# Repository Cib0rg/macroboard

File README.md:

# ESP32-S3 Macro Keyboard

Программируемая макроклавиатура с открытым исходным кодом на базе ESP32-S3 — 10 кнопок с индивидуальными круглыми дисплеями, RGB подсветкой и настраиваемыми действиями.

## Обзор

Устройство аналогично Elgato Stream Deck, но с открытым исходным кодом. Каждая кнопка имеет собственный круглый дисплей 160×160 для отображения иконок, RGB LED подсветку и программируемое действие.
Отсутствует ограничение по входному напряжению, подключение зарядок с QC скорее всего сожжёт часть платы!
Включать сначала питание от 2А блока (нижний разъём), потом уже подключать ESP через встроенные. Иначе есть небольшой шанс выхода из строя DC-DC преобразователя на плате ESP.

## Реализованные возможности

### Прошивка (Firmware)

- ✅ **Драйвер дисплеев GC9A01** — 10 круглых дисплеев 160×160 через SPI с мультиплексором 2× 74HC138
- ✅ **PWM подсветка дисплеев** — регулировка яркости 0-255 через LEDC
- ✅ **WS2812 RGB LED** — индивидуальная подсветка каждой кнопки с настройкой цвета и яркости
- ✅ **USB Composite Device** — HID Keyboard + Consumer Control + Vendor Bulk (TinyUSB)
- ✅ **Протокол обмена** — 64-байтовые пакеты через Vendor Bulk endpoint
- ✅ **Конфигурация** — хранение настроек кнопок и энкодера в LittleFS
- ✅ **Папки** — вложенные папки кнопок (до 8 уровней глубины)
- ✅ **Передача изображений** — JPEG изображения на кнопки с дедупликацией по CRC32
- ✅ **Асинхронная запись LittleFS** — `save_task` на Core 0, очередь 20 слотов; протокол не блокируется на I/O, sync fallback при нехватке слотов; полная синхронизация ~17 изображений: ~11 с вместо ~39 с
- ✅ **LittleFS хранилище текстов** — тексты до 4096 байт в LittleFS по 5-компонентному ключу `(profile/folder/button/action_slot/step_index)`; покрывает: Keyboard > 44 байт, long press Keyboard, каждый шаг Sequence с длинным текстом, Sequence-блоб > 51 байт
- ✅ **Rotary encoder** — настраиваемые действия на CW/CCW/нажатие/долгое нажатие
- ✅ **Долгое нажатие** — отдельное действие и название для каждой кнопки (корневой и в папках)
- ✅ **Debounced кнопки** — обработка нажатий через прерывания с программным debounce
- ✅ **Действия кнопок**: Keyboard, Media (Consumer Control), Shell, Folder, Sequence, CustomHID, LaunchApp, NightMode

### Управляющий софт (Software)

- ✅ **Кроссплатформенный UI** — Avalonia UI (Linux, Windows, macOS)
- ✅ **Backend Service** — фоновый сервис для связи с устройством
- ✅ **IPC** — TCP-based коммуникация между UI и Backend с автоматическим переподключением
- ✅ **Редактор конфигурации** — создание, редактирование, синхронизация конфигураций с устройством (JSON)
- ✅ **Конфигурация кнопок** — inline-редактор с поддержкой всех типов действий
- ✅ **Захват клавиш** — запись комбинаций клавиш в реальном времени
- ✅ **Последовательности действий** — до 16 шагов с задержками
- ✅ **Медиа-клавиши** — Volume Up/Down, Mute, Play/Pause, Next/Prev Track
- ✅ **Превью изображений** — миниатюры в списке кнопок и превью в редакторе
- ✅ **Настройка LED** — выбор цвета через ColorPicker, яркость
- ✅ **Настройка подсветки дисплеев** — слайдер яркости в Dashboard и Settings
- ✅ **Tray icon** — работа в фоне, сворачивание в трей
- ✅ **Dashboard** — статус устройства, лог событий, управление яркостью
- ✅ **Diff-based синхронизация профиля** — при Send пересылаются только изменённые кнопки; fingerprint учитывает image path+mtime, action type+JSON, LED; типовая правка одной кнопки: ~5 с; холодная синхронизация ~17 изображений: ~11 с (async SPIFFS)
- ✅ **Синхронизация с устройством** — отправка/загрузка профилей через USB
- ✅ **Сохранение профиля** — Save пишет в исходный файл (откуда был загружен через Load), а не в AppData
- ✅ **LibUsbDotNet** — кроссплатформенная USB коммуникация (Linux/Windows/macOS)
- ✅ **Плагины (Stream Deck совместимость)** — запуск `.streamDeckPlugin` архивов и исполняемых плагинов, WebSocket API на порту 28196, Property Inspector на порту 8787; плагины хранятся в `plugins/` рядом с бинарником бэкенда
- ✅ **Валидация ввода** — Shell-команда ≤ 49 байт UTF-8, Custom HID ≤ 51 байт (соответствует `ACTION_DATA_MAX_LEN` прошивки); превышение показывает ошибку вместо молчаливой обрезки
- ✅ **Кэш иконок приложений** — иконки извлекаются один раз через P/Invoke и сохраняются в `%APPDATA%\MacroKeyboard\icons\`; повторное открытие диалога не вызывает P/Invoke

## Плагины

MacroKeyboard поддерживает плагины в стиле Elgato Stream Deck. Каждая кнопка может быть привязана к действию стороннего плагина, который получает события нажатий и управляет дисплеем.

Два режима работы:
- **Executable** — отдельный процесс на любом языке (C#, Node.js, Python), общается с бекендом через WebSocket на порту 28196.
- **Managed** — .NET DLL, загружается в процесс бекенда, получает прямой доступ к устройству через `IPlugin` / `IPluginContext`.

Плагины кладутся в папку `plugins/` рядом с бинарником бекенда в виде директории или `.zip`-архива с расширением `.sdPlugin`. Существующие плагины для Stream Deck работают с минимальными изменениями.

Подробное руководство по разработке плагинов: **[PLUGIN_DEVELOPMENT.html](PLUGIN_DEVELOPMENT.html)**

## Структура проекта

```
elgato/
├── firmware/                    # Прошивка ESP32-S3 (ESP-IDF v5.4, C)
│   └── main/
│       ├── hardware/            # Драйверы: дисплеи, LED, кнопки, энкодер
│       ├── profile/             # Менеджер профилей, исполнитель действий
│       ├── protocol/            # Обработчик протокола, передача изображений и текста
│       ├── storage/             # NVS, LittleFS, профили, изображения, длинный текст, async save_task
│       └── usb/                 # USB дескрипторы, HID keyboard, vendor endpoint
│
├── hardware/                    # Аппаратная часть
│   ├── case/                    # 3D-модели корпуса (OpenSCAD + STL для печати)
│   └── pcb/                     # Схемотехника и разводка PCB (KiCad)
│
├── software/                    # Управляющее приложение (.NET 10, C#)
│   └── src/
│       ├── MacroKeyboard.Core/          # Модели, IPC, интерфейсы сервисов
│       ├── MacroKeyboard.Communication/ # USB протокол, команды устройства
│       ├── MacroKeyboard.Infrastructure/# Реализация сервисов, репозитории
│       ├── MacroKeyboard.Backend/       # Фоновый сервис (IPC сервер, роутинг)
│       └── MacroKeyboard.UI/            # Avalonia UI (MVVM, CommunityToolkit)
│
└── plans/                       # Проектная документация
```

## Быстрый старт

### Сборка прошивки

```bash
cd firmware
# Через Docker (рекомендуется):
docker run --rm -v "$(pwd)":/project -w /project espressif/idf:v5.4 idf.py build
# Или локально с установленным ESP-IDF v5.4:
idf.py build
idf.py flash
```

### Сборка софта

```bash
cd software
dotnet build MacroKeyboard.sln
# Запуск Backend:
dotnet run --project src/MacroKeyboard.Backend
# Запуск UI:
dotnet run --project src/MacroKeyboard.UI
```

### Linux: доступ к USB без root

```bash
sudo cp software/scripts/99-macrokeyboard.rules /etc/udev/rules.d/
sudo udevadm control --reload-rules
```

## Технологии

### Прошивка

| Компонент | Технология |
|-----------|-----------|
| Платформа | ESP32-S3 N16R8 (16MB Flash, 8MB PSRAM) |
| Framework | ESP-IDF v5.4 |
| RTOS | FreeRTOS |
| USB | TinyUSB (HID + Vendor composite) |
| Язык | C99 |

### Софт

| Компонент | Технология |
|-----------|-----------|
| Runtime | .NET 10 |
| UI | Avalonia UI 12 |
| Архитектура | MVVM (CommunityToolkit.Mvvm) |
| USB | LibUsbDotNet 3.x |
| Изображения | SixLabors.ImageSharp |
| Сериализация | Newtonsoft.Json |
| Логирование | Serilog |

## Аппаратные компоненты

| Компонент | Модель | Кол-во | Примечания |
|-----------|--------|--------|------------|
| Микроконтроллер | ESP32-S3 N16R8 | 1 | 16MB Flash, 8MB PSRAM |
| Дисплей | GC9A01 160×160 | 10 | Круглые TFT, SPI |
| Кнопки | Тактовые | 10 | GPIO с прерываниями |
| RGB LED | WS2812 | 10 | Адресные, RMT peripheral |
| Энкодер | Rotary encoder | 1 | С кнопкой |
| Мультиплексор | 74HC138 | 2 | Выбор дисплея (5+5) |

Схемотехника и разводка PCB находятся в директории [`hardware/pcb/`](hardware/pcb/) (формат KiCad).
3D-модели корпуса для печати — в [`hardware/case/`](hardware/case/) (OpenSCAD + STL).

## Протокол обмена данными

64-байтовые пакеты через USB Vendor Bulk endpoint:

```
[0]    Magic (0xA5)
[1]    Command ID
[2-3]  Payload Length
[4-5]  Sequence Number
[6-61] Payload (56 bytes)
[62]   Checksum (XOR)
[63]   End Byte (0x5A)
```

### Команды

| ID | Команда | Описание |
|----|---------|----------|
| 0x01 | PING | Проверка связи |
| 0x02 | GET_DEVICE_INFO | Информация об устройстве |
| 0x10 | SET_PROFILE | Активировать профиль |
| 0x11–0x12 | GET_PROFILE_INFO / FOLDER_STATE | Состояние профиля и текущей папки |
| 0x20–0x22 | IMAGE_TRANSFER | Передача изображений (start/chunk/end) |
| 0x30–0x34 | BUTTON_ACTION/NAME | Установка действия и имени кнопки (корневые и папки) |
| 0x35 | SET_ENCODER_ACTION | Настройка действий энкодера |
| 0x36–0x37 | LONG_PRESS_ACTION/NAME | Действие и название долгого нажатия |
| 0x38–0x3A | TEXT_TRANSFER | Передача текста/блоба в SPIFFS (start/chunk/end); Keyboard > 44 байт, long press, Sequence-шаги и блобы > 51 байт |
| 0x40–0x43 | LED/BACKLIGHT | Управление LED и подсветкой дисплеев |
| 0x50–0x53 | PROFILE_SAVE/LOAD/DELETE/REFRESH | Управление профилями и обновление дисплеев |

### Типы действий

| ID | Тип | Описание |
|----|-----|----------|
| 0x01 | Keyboard | Эмуляция клавиатуры; текст ≤ 44 байт — inline, > 44 байт — SPIFFS |
| 0x02 | CustomHID | Произвольный HID report |
| 0x04 | Folder | Открытие папки кнопок |
| 0x06 | Shell | Выполнение shell-команды на PC |
| 0x07 | Sequence | Последовательность до 16 действий |
| 0x08 | LaunchApp | Запуск приложения на PC |
| 0x09 | Media | Медиа-клавиши (Volume, Mute, Play/Pause и др.) |
| 0x0A | NightMode | Переключение ночного режима (снижение яркости) |
| 0x0B | Plugin | Действие стороннего плагина (Stream Deck-совместимого) |

### LittleFS-хранилище текстов

Команды 0x38–0x3A передают текстовые данные, которые не влезают inline. На устройстве файл называется `/storage/txt_{P}_{F}_{B}_{A}_{S}.bin`, где:

| Поле | Смысл |
|------|-------|
| P | profile_id (всегда 0) |
| F | folder_id: 0..15 = папка, 255 = root |
| B | button_id: 0..9; энкодер: 0x40–0x43 |
| A | action slot: 0 = short press, 1 = long press |
| S | step: 0xFF = прямое Keyboard, 0xFE = Sequence-блоб, 0..15 = шаг Sequence |

Что хранится в SPIFFS:
- **Keyboard** текст > 44 байт — `step=0xFF` (short), `step=0xFF, slot=1` (long press)
- **Sequence-шаг Keyboard** > 44 байт — `step=N` (индекс шага)
- **Sequence-блоб** > 51 байт — `step=0xFE`; в `action_data` кнопки записывается маркер `[0x01]`

ПО автоматически выбирает между inline и SPIFFS. Payload CMD_SET_BUTTON_TEXT_START: 9 байт — `[profile_id][folder_id][button_id][action_slot][step_index][data_size(4 LE)]`.

## Лицензия

WTFPL

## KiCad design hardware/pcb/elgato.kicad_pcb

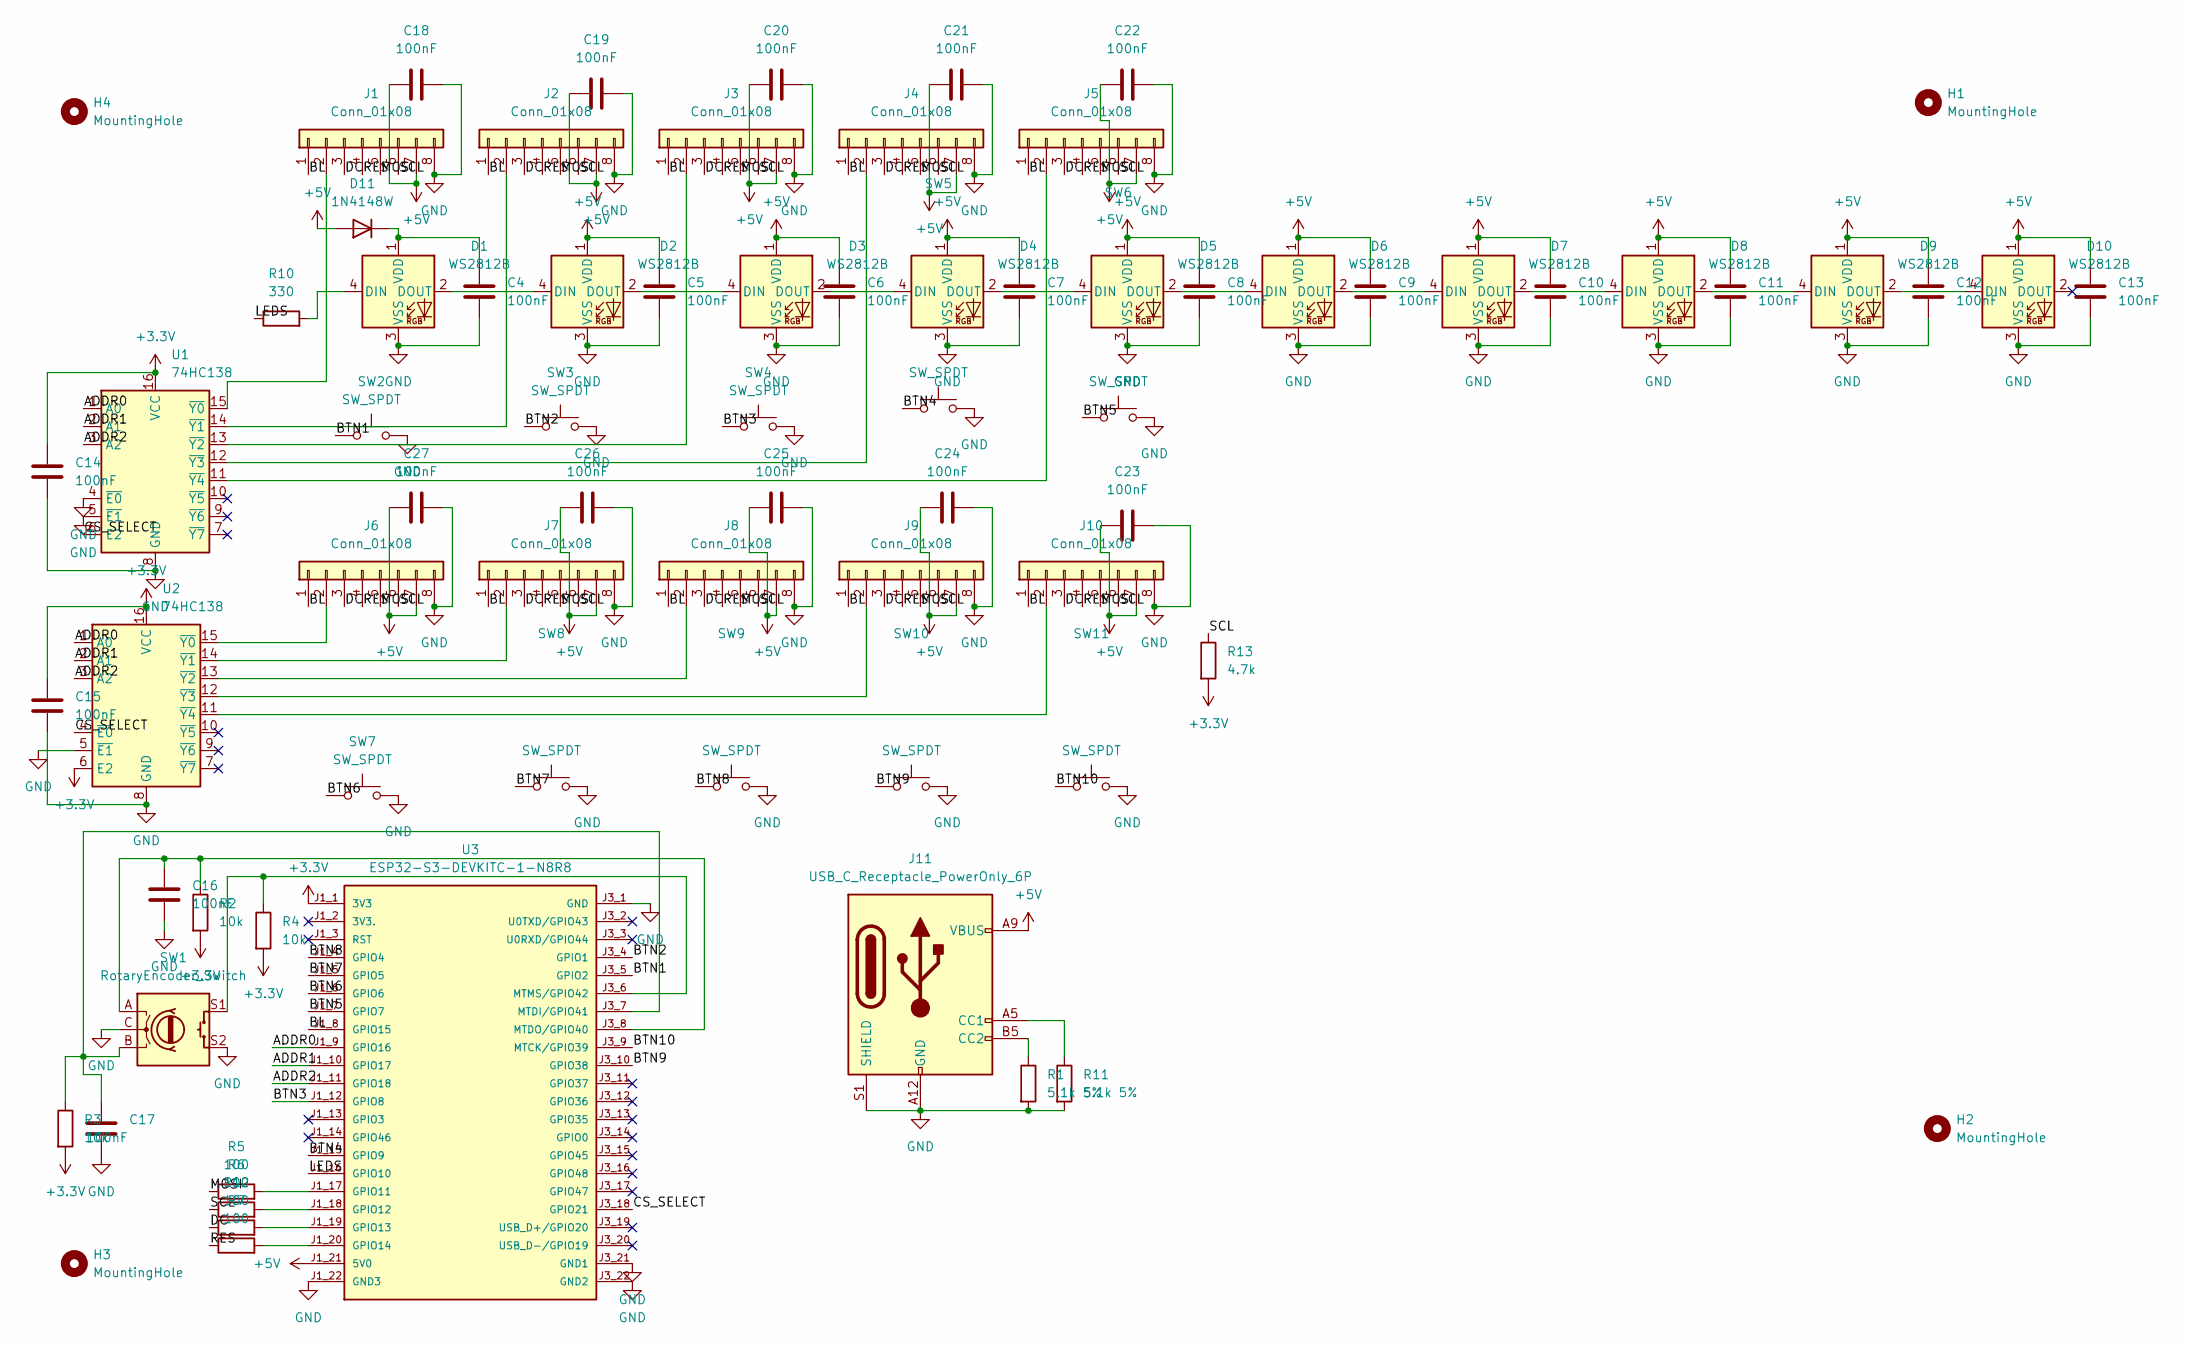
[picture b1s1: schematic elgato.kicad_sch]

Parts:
C4, C5, C6, C7, C8, C9, C10, C11, C12, C13, C14, C15, C16, C17, C18, C19, C20, C21, C22, C23, C24, C25, C26, C27: 100nF; C_0805_2012Metric; LCSC C710980
D1, D2, D3, D4, D5, D6, D7, D8, D9, D10: WS2812B; LED_WS2812B_PLCC4_5.0x5.0mm_P3.2mm; LCSC C52917433
D11: 1N4148W; D_SOD-123; LCSC C83528
H1, H2, H3, H4: MountingHole; MountingHole_3.2mm_M3
J1, J2, J3, J4, J5, J6, J7, J8, J9, J10: Conn_01x08; PinHeader_1x08_P2.54mm_Vertical
J11: USB_C_Receptacle_PowerOnly_6P; USB_C_Receptacle_HRO_TYPE-C-31-M-17; LCSC C283540
R1, R11: 5.1k 5%; R_0805_2012Metric; LCSC C2912599
R2, R3, R4: 10k; R_0805_2012Metric; LCSC C5123591
R5, R6, R7, R12: 100; R_0805_2012Metric; LCSC C2912614
R10: 330; R_0805_2012Metric; LCSC C2558024
R13: 4.7k; R_Axial_DIN0204_L3.6mm_D1.6mm_P5.08mm_Horizontal
SW1: RotaryEncoder_Switch; RotaryEncoder_Alps_EC11E-Switch_Vertical_H20mm
SW2, SW3, SW4, SW5, SW6, SW7, SW8, SW9, SW10, SW11: SW_SPDT; SW_Cherry_MX_1.00u_PCB
U1, U2: 74HC138; SOIC-16_3.9x9.9mm_P1.27mm; LCSC C6818
U3: ESP32-S3-DEVKITC-1-N8R8

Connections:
+3.3V: C14.1, C15.1, R2.2, R3.2, R4.2, R13.2, U1.16 (VCC), U2.6 (E2), U2.16 (VCC), U3.J1_1 (3V3)
+5V: C5.1, C6.1, C7.1, C8.1, C9.1, C10.1, C11.1, C12.1, C13.1, C18.1, C19.1, C20.1, C21.1, C22.1, C23.1, C24.1, C25.1, C26.1, C27.1, D2.1 (VDD), D3.1 (VDD), D4.1 (VDD), D5.1 (VDD), D6.1 (VDD), D7.1 (VDD), D8.1 (VDD), D9.1 (VDD), D10.1 (VDD), D11.2 (A), J1.7, J2.7, J3.7, J4.7, J5.7, J6.7, J7.7, J8.7, J9.7, J10.7, J11.A9 (VBUS), J11.B9 (VBUS), U3.J1_21 (5V0); also elsewhere on the board
/ADDR0: U1.1 (A0), U2.1 (A0), U3.J1_9 (GPIO16)
/ADDR1: U1.2 (A1), U2.2 (A1), U3.J1_10 (GPIO17)
/ADDR2: U1.3 (A2), U2.3 (A2), U3.J1_11 (GPIO18)
/BL: J1.1, J2.1, J3.1, J4.1, J5.1, J6.1, J7.1, J8.1, J9.1, J10.1, U3.J1_8 (GPIO15)
/BTN1: SW2.1, U3.J3_5 (GPIO2)
/BTN2: SW3.1, U3.J3_4 (GPIO1)
/BTN3: SW4.1, U3.J1_12 (GPIO8)
/BTN4: SW5.1, U3.J1_15 (GPIO9)
/BTN5: SW6.1, U3.J1_7 (GPIO7)
/BTN6: SW7.1, U3.J1_6 (GPIO6)
/BTN7: SW8.1, U3.J1_5 (GPIO5)
/BTN8: SW9.1, U3.J1_4 (GPIO4)
/BTN9: SW10.1, U3.J3_10 (GPIO38)
/BTN10: SW11.1, U3.J3_9 (MTCK/GPIO39)
/CS_SELECT: U1.6 (E2), U2.4 (~E0), U3.J3_18 (GPIO21)
/DC: J1.3, J2.3, J3.3, J4.3, J5.3, J6.3, J7.3, J8.3, J9.3, J10.3, R12.1
/LEDS: R10.1, U3.J1_16 (GPIO10)
/MOSI: J1.5, J2.5, J3.5, J4.5, J5.5, J6.5, J7.5, J8.5, J9.5, J10.5, R5.1
/RES: J1.4, J2.4, J3.4, J4.4, J5.4, J6.4, J7.4, J8.4, J9.4, J10.4, R7.1
/SCL: J1.6, J2.6, J3.6, J4.6, J5.6, J6.6, J7.6, J8.6, J9.6, J10.6, R6.1, R13.1
GND: C4.2, C5.2, C6.2, C7.2, C8.2, C9.2, C10.2, C11.2, C12.2, C13.2, C14.2, C15.2, C16.2, C17.2, C18.2, C19.2, C20.2, C21.2, C22.2, C23.2, C24.2, C25.2, C26.2, C27.2, D1.3 (VSS), D2.3 (VSS), D3.3 (VSS), D4.3 (VSS), D5.3 (VSS), D6.3 (VSS), D7.3 (VSS), D8.3 (VSS), D9.3 (VSS), D10.3 (VSS), J1.8, J2.8, J3.8, J4.8, J5.8, J6.8, J7.8, J8.8, J9.8, J10.8, J11.A12 (GND), J11.B12 (GND), J11.S1 (SHIELD), R1.2, R11.2, SW1.C, SW1.S2, SW2.2, SW3.2, SW4.2, SW5.2, SW6.2, SW7.2, SW8.2, SW9.2, SW10.2, SW11.2, U1.4 (~E0), U1.5 (~E1), U1.8 (GND), U2.5 (~E1), U2.8 (GND), U3.J1_22 (GND3), U3.J3_1 (GND), U3.J3_21 (GND1), U3.J3_22 (GND2); also elsewhere on the board
unnamed: D1.4 (DIN), R10.2
unnamed: D1.2 (DOUT), D2.4 (DIN)
unnamed: C4.1, D1.1 (VDD), D11.1 (K)
unnamed: D2.2 (DOUT), D3.4 (DIN)
unnamed: D3.2 (DOUT), D4.4 (DIN)
unnamed: D4.2 (DOUT), D5.4 (DIN)
unnamed: D5.2 (DOUT), D6.4 (DIN)
unnamed: D6.2 (DOUT), D7.4 (DIN)
unnamed: D7.2 (DOUT), D8.4 (DIN)
unnamed: D8.2 (DOUT), D9.4 (DIN)
unnamed: D9.2 (DOUT), D10.4 (DIN)
unnamed: J1.2, U1.15 (~Y0)
unnamed: J2.2, U1.14 (~Y1)
unnamed: J3.2, U1.13 (~Y2)
unnamed: J4.2, U1.12 (~Y3)
unnamed: J5.2, U1.11 (~Y4)
unnamed: J6.2, U2.15 (~Y0)
unnamed: J7.2, U2.14 (~Y1)
unnamed: J8.2, U2.13 (~Y2)
unnamed: J9.2, U2.12 (~Y3)
unnamed: J10.2, U2.11 (~Y4)
unnamed: J11.A5 (CC1), R11.1
unnamed: J11.B5 (CC2), R1.1
unnamed: R5.2, U3.J1_17 (GPIO11)
unnamed: R6.2, U3.J1_18 (GPIO12)
unnamed: R12.2, U3.J1_19 (GPIO13)
unnamed: R7.2, U3.J1_20 (GPIO14)
unnamed: C17.1, R3.1, SW1.B, U3.J3_7 (MTDI/GPIO41)
unnamed: C16.1, R2.1, SW1.A, U3.J3_8 (MTDO/GPIO40)
unnamed: R4.1, SW1.S1, U3.J3_6 (MTMS/GPIO42)

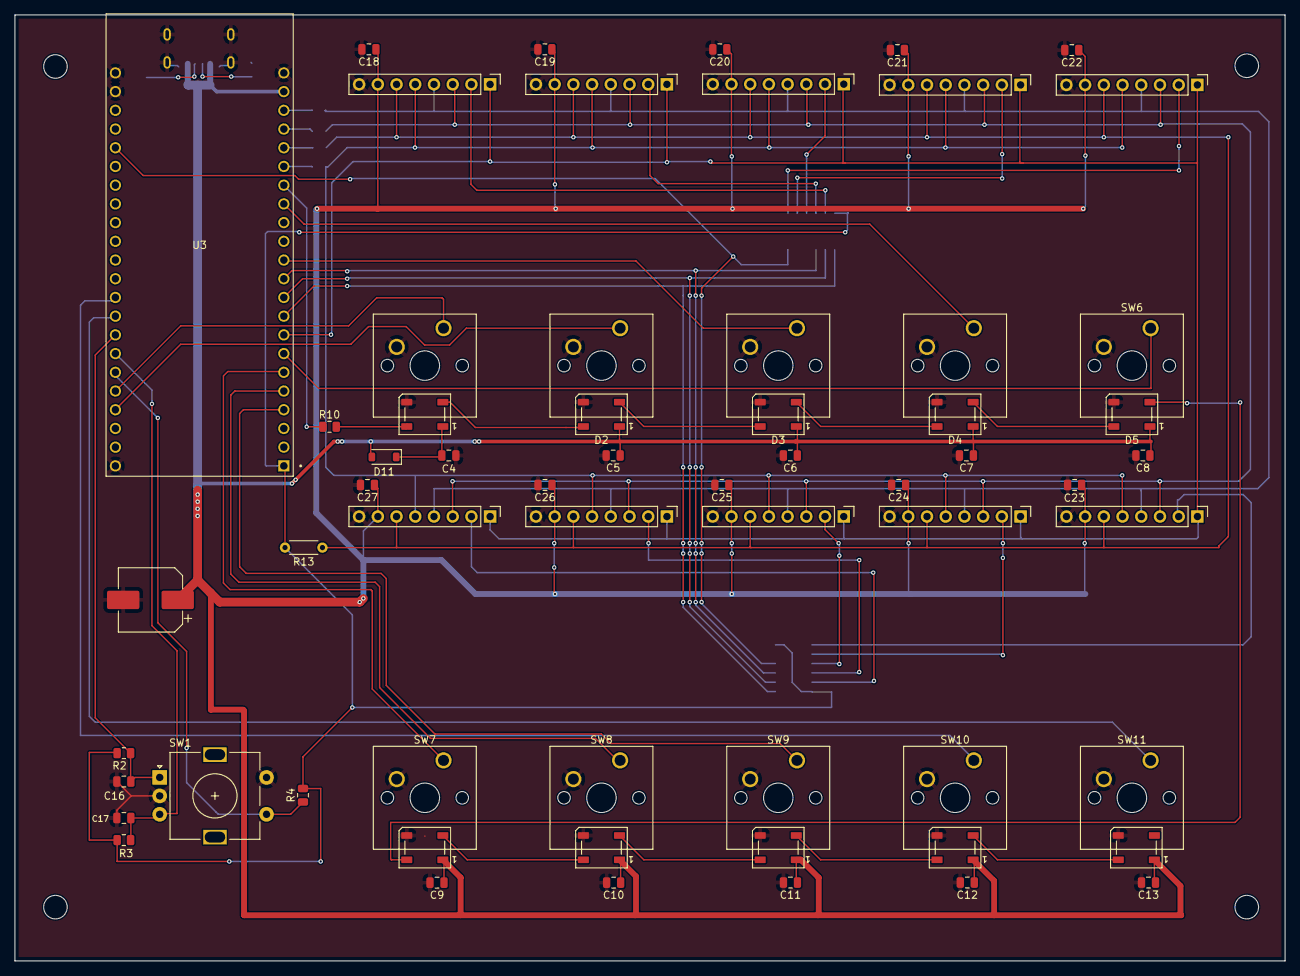
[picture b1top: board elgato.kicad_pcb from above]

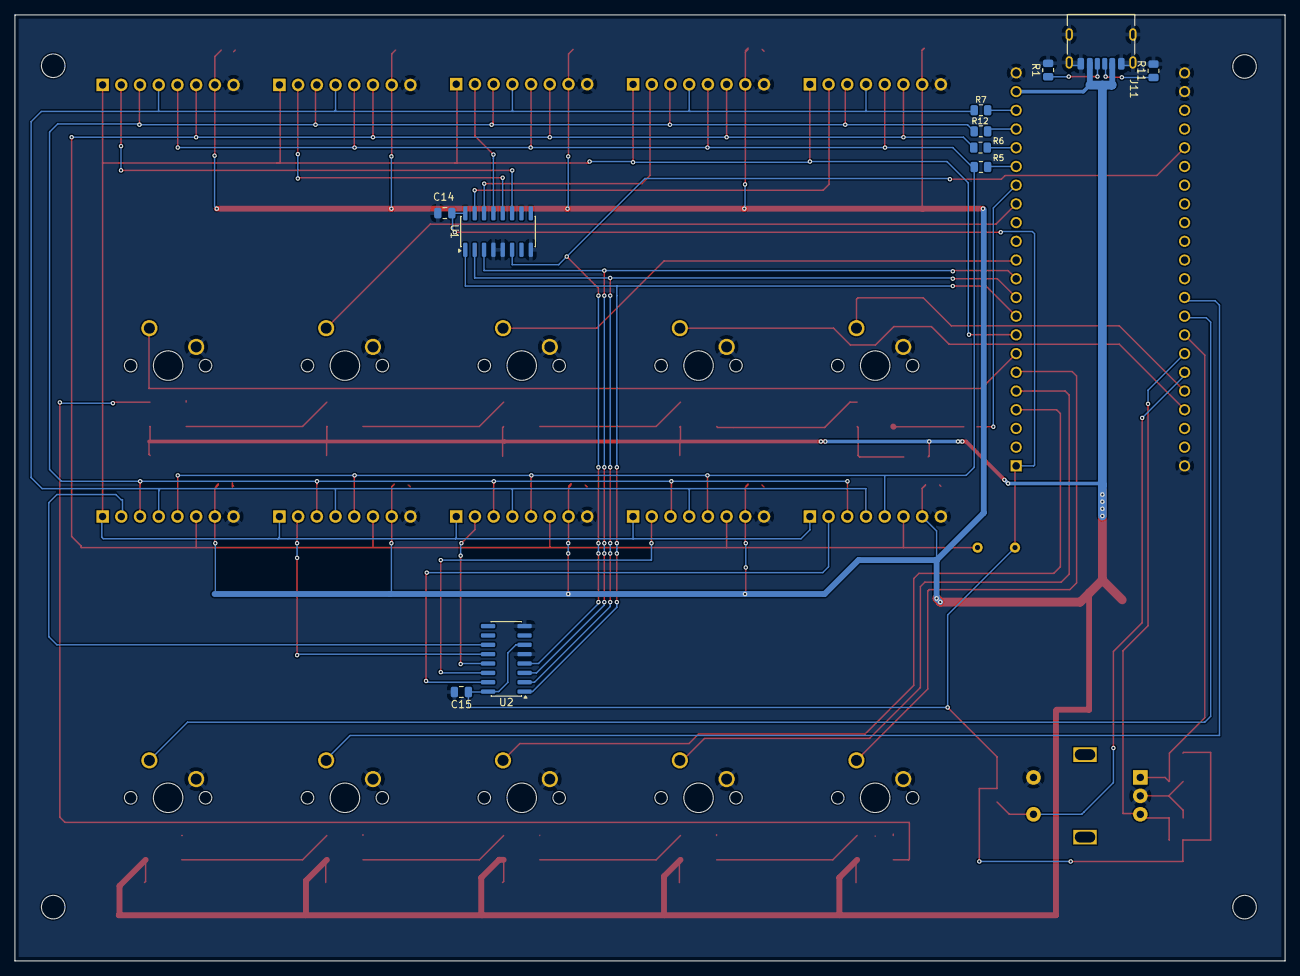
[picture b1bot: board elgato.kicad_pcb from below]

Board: 2 copper layers, 172.4 x 128.4 mm, 76 parts (11 on the bottom side), 53 nets.

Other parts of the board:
C1: 470uF 10V; CP_Elec_8x10.5

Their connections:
+5V: C1.1; also elsewhere on the board
GND: C1.2; also elsewhere on the board

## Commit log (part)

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2026-03-25 Initial wipecoding commmit
2026-03-25 Store basic concept before start to code
2026-03-25 Before development
2026-03-26 Compiled but buggy
2026-04-12 Firmware almost work
2026-04-12 Work
2026-04-12 fix: Add proper gitignore
2026-04-12 Stop tracking build artifacts
2026-04-12 feat: Proper function of firmware
2026-04-13 Clean all todos
2026-04-14 Add example to gitignore
2026-04-14 Add some docs
2026-04-14 Remove build artifact from git
2026-04-14 Store all project, bump dotnet to 10
2026-04-15 Store changes
2026-04-19 feat: Now this is two-headed device
2026-04-19 fix: Storing plans and status
2026-04-21 feat: working connection
2026-04-21 fix: Fixed device connect status in UI
2026-04-22 Cleanup
2026-04-22 fix: Add reconnect support
2026-04-22 fix: Fixes for HID device + stack overflow
2026-04-23 Fixing bugs and making plans
2026-04-24 Some cleanup
2026-04-24 fix: Readme and mux fixes
2026-04-24 Add fantasies
2026-04-24 Bumping gitignore
2026-04-27 Extract styles
2026-04-27 feat: Test Tron UI
2026-04-30 feat: More towards ColorPicker
2026-04-30 feat: Capture keys for kbd
2026-05-01 feat: Add Styles and sequence executor
2026-05-01 fix: Remove warnings
2026-05-03 feat: Delete buttonconfig dialog
2026-05-04 Working on UI
2026-05-04 fix: Fixes for KB for windows
2026-05-05 feat: New icon + new action Exec + ColorPicker
2026-05-05 feat: Profiles have names
2026-05-06 fix: Add name to folders
2026-05-06 fix: Add Key capture to sequence
2026-05-06 feat: Add more image types
2026-05-06 feat: Add text if there is no images for button
2026-05-11 fix: Fixing LEDS
2026-05-13 fix: Fixing work with profiles
2026-05-14 fix: Working TZT + debug
2026-05-15 fix: SPI speed down to 20MHz (because of ringind)
2026-05-15 chore: New plans
2026-05-20 feat: Add image dedup + proper USB handling
2026-05-20 feat: Add installer base
2026-05-20 fix: Add UI-backend reconnect
2026-05-20 feat: Add images preview
2026-05-23 feat: Add SPI brighteness control
2026-05-25 feat: USB library fix + media action
2026-05-25 feat: Add hardware related files
2026-05-25 chore: Add some specs
2026-05-25 chore: Edit docs
2026-05-26 chore: Modify readme
2026-05-26 chore: Remove obsolette files
2026-05-26 fix: Set recursion depth to 8
2026-05-30 fix: Add encoder setup + text input fix
2026-05-30 fix: Fixed USB wait timeout
2026-05-30 fix: Minor fix for profiles
2026-05-30 chore: Some cleanup
2026-06-07 feat: Add text to displays if there is no image
2026-06-07 feat: Add night mode
2026-06-07 fix: Set brightness in UI to 0-100 instead of 0-255
2026-06-08 fix: Fixed cover (top and bottom)
2026-06-09 feat: Add 45 degrees stand model
2026-06-10 feat: Installer + README + bugfixing
2026-06-10 fix: Block back button
2026-06-10 feat: Add scripts for windows build
2026-06-10 fix: Fixes fot folder-related bugs
2026-06-10 fix: Increase slability
2026-06-10 fix: Fixes for icons on Launch app button
2026-06-11 fix: Fixes for exec
2026-06-11 fix: Fixed bug with no reconnects between UI and backend
2026-06-11 fix: Fixes for screen-related bugs
2026-06-11 feat: Add image GC
2026-06-11 cleanup: Remove obsolette project
2026-06-11 fix: Visual bug fix (UI)
2026-06-11 chore: Add docs for building
2026-06-11 fix: Remove profiles
2026-06-12 feat: Long press setup + night mode fixes
2026-06-12 fix: Change Folder back icon
2026-06-12 fix: Fixing profile storage bug
2026-06-12 feat: Add parallel build for windows
2026-06-12 fix: Fixing GPU consumation for UI
2026-06-12 plans: Add plans for implementation of plugin system
2026-06-12 feat: Marks for long press + encoder fix
2026-06-13 fix: Fixes for encoder setup (UI)
2026-06-13 chore: Add .claude to .gitignore
2026-06-13 refactor: Docs refactor
2026-06-13 feat: Plans + start work on plugin system
2026-06-13 feat: UI 2.0
2026-06-14 fix: Slightly change long click behaviour
2026-06-15 feat: Big feature: StreamDeck plugin system compatibility
2026-06-15 feat: Screens speedup, folder long press fix + other fixes
2026-06-15 feat: Add \n and other symbols to KB action
2026-06-15 feat: Add buttons swap using drag-n-drop
2026-06-15 fix: Fixes for small visual bugs
2026-06-16 fix: Change starting screen
2026-06-16 feat: Add backend reload for plugins manipulation
2026-06-16 fix: Several bugs fixed
2026-06-17 fix: Several fixes for save profile and image transfer
2026-06-17 fix: KB text size update + readme update
2026-06-21 feat: Major changes (see description)
    - change protocol to improve speed and stability
    - change SPI work protocol to improve stability
    - add HomeAssistant plugin to switch entities from macroboard
2026-06-22 fix: Several stability related fixes + protocol speedup
2026-06-24 feat: Add Heartbeat to make reconnect possible
2026-06-24 chore: Update README
2026-06-24 chore: Update REFERENCE
2026-06-25 refactor: Compacting code of firmware (still WIP)
2026-06-25 refactor: Compacting code of firmware (2/3)
2026-06-25 refactor: Compacting code of firmware (3/3)
2026-06-25 fix: Fixes for LCDs after refactor
2026-06-25 fix: Fixes for SPIFFS store bugs
2026-06-25 refactor: Backend refactoring (1/2)
2026-06-26 refactor: Backend refactoring (2/2)
2026-06-26 refactor: UI refactoring (1/2)
2026-06-26 refactor: UI refactoring (3/3)
2026-06-27 chore: Update docs
2026-06-29 fix: Fixes for updates from plugin
2026-06-29 fix: Fixes for plugins in folder
2026-06-30 fix: Fixes for HA plugin

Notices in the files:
README.md:
License: TBD
